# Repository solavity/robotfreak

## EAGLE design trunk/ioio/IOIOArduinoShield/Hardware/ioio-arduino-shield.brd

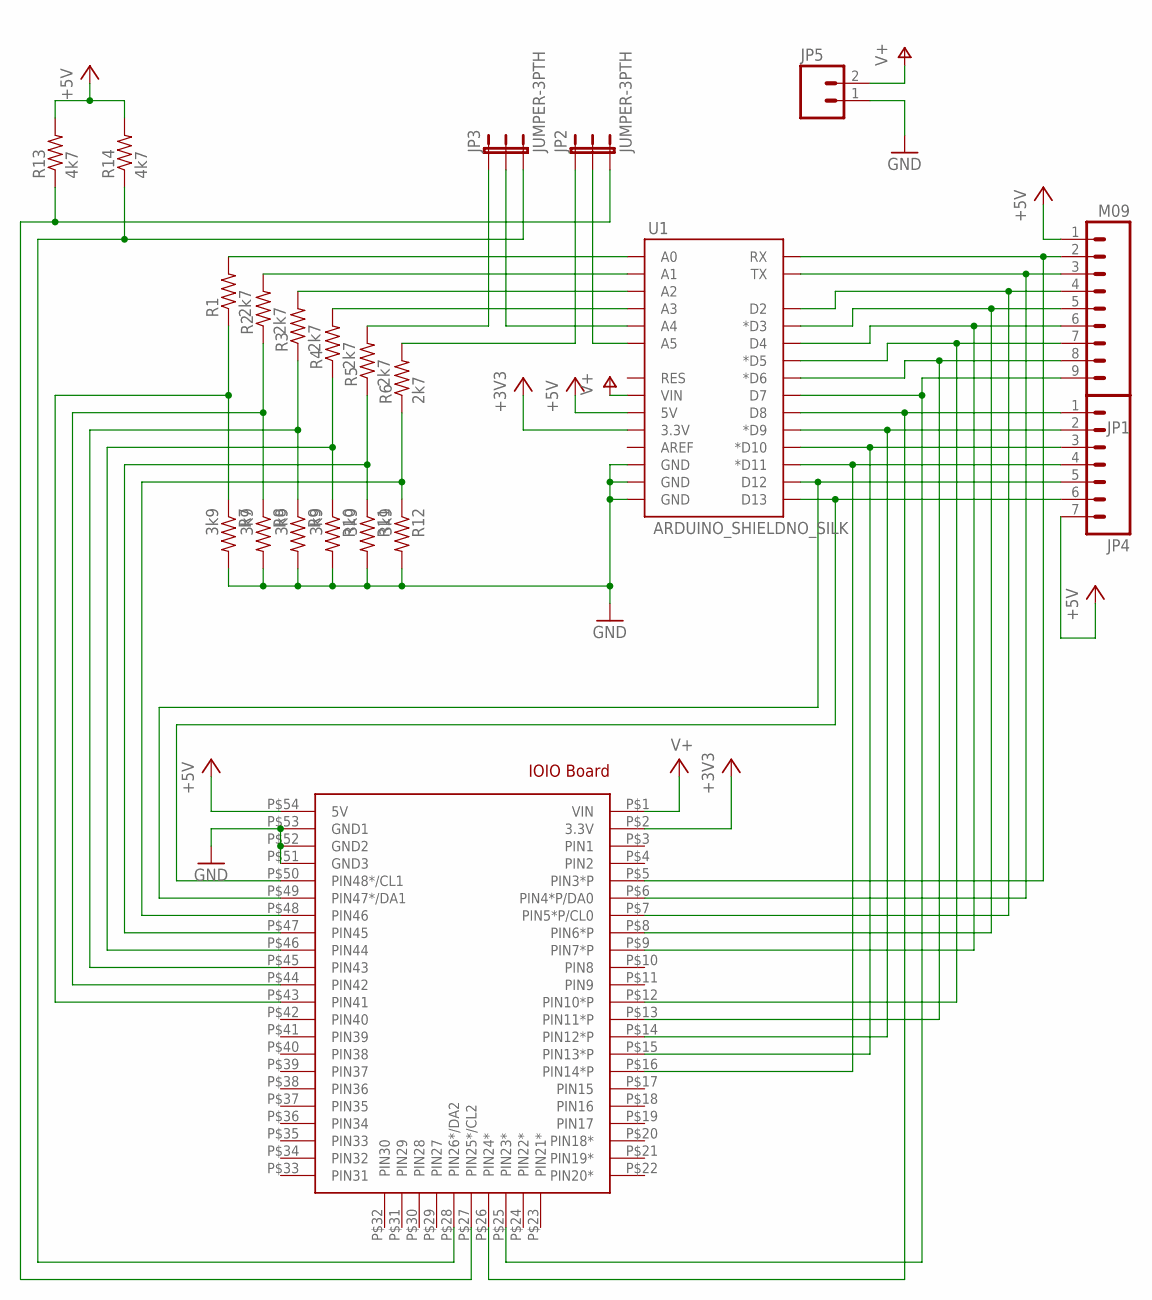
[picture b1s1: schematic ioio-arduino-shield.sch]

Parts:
JP1: M09; 1X09
JP2, JP3: JUMPER-3PTH; 1X03
JP4: M07; 1X07
JP5: M025MM; SCREWTERMINAL-5MM-2
R1, R2, R3, R4, R5, R6: 2k7; 0805
R7, R8, R9, R10, R11, R12: 3k9; 0805
R13, R14: 4k7; 0805
U1: ARDUINO_SHIELDNO_SILK; DUEMILANOVE_VIAS
U$1: IOIO

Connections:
+3V3: U1.3.3V, U$1.P$2 (3.3V)
+5V: JP1.1, JP4.7, R13.2, R14.2, U1.5V, U$1.P$54 (5V)
GND: JP5.1, R7.2, R8.2, R9.2, R10.2, R11.2, R12.2, U1.GND@0 (GND), U1.GND@1 (GND), U1.GND@2 (GND), U$1.P$51 (GND3), U$1.P$52 (GND2), U$1.P$53 (GND1)
unnamed: R1.2, U1.A0
unnamed: R2.2, U1.A1
unnamed: R3.2, U1.A2
unnamed: R4.2, U1.A3
unnamed: JP3.1, R5.2
unnamed: JP3.2, U1.A4
unnamed: JP2.1, R6.2
unnamed: JP2.2, U1.A5
unnamed: R1.1, R7.1, U$1.P$43 (PIN41)
unnamed: JP1.2, U1.RX, U$1.P$5 (PIN3*P)
unnamed: JP1.3, U1.TX, U$1.P$6 (PIN4*P/DA0)
unnamed: JP1.4, U1.D2, U$1.P$7 (PIN5*P/CL0)
unnamed: JP1.5, U1.D3 (*D3), U$1.P$8 (PIN6*P)
unnamed: U1.D4, U$1.P$9 (PIN7*P)
unnamed: JP1.7, U1.D5 (*D5), U$1.P$12 (PIN10*P)
unnamed: JP1.8, U1.D6 (*D6), U$1.P$13 (PIN11*P)
unnamed: JP4.1, U1.D8, U$1.P$26 (PIN24*)
unnamed: JP4.2, U1.D9 (*D9), U$1.P$14 (PIN12*P)
unnamed: JP4.3, U1.D10 (*D10), U$1.P$15 (PIN13*P)
unnamed: JP4.4, U1.D11 (*D11), U$1.P$16 (PIN14*P)
unnamed: JP4.5, U1.D12, U$1.P$49 (PIN47*/DA1)
unnamed: JP4.6, U1.D13, U$1.P$50 (PIN48*/CL1)
unnamed: R2.1, R8.1, U$1.P$44 (PIN42)
unnamed: R3.1, R9.1, U$1.P$45 (PIN43)
unnamed: R4.1, R10.1, U$1.P$46 (PIN44)
unnamed: R5.1, R11.1, U$1.P$47 (PIN45)
unnamed: R6.1, R12.1, U$1.P$48 (PIN46)
unnamed: U1.D7, U$1.P$25 (PIN23*)
unnamed: JP2.3, R13.1, U$1.P$27 (PIN25*/CL2)
unnamed: JP3.3, R14.1, U$1.P$28 (PIN26*/DA2)
V+: JP5.2, U1.VIN, U$1.P$1 (VIN)

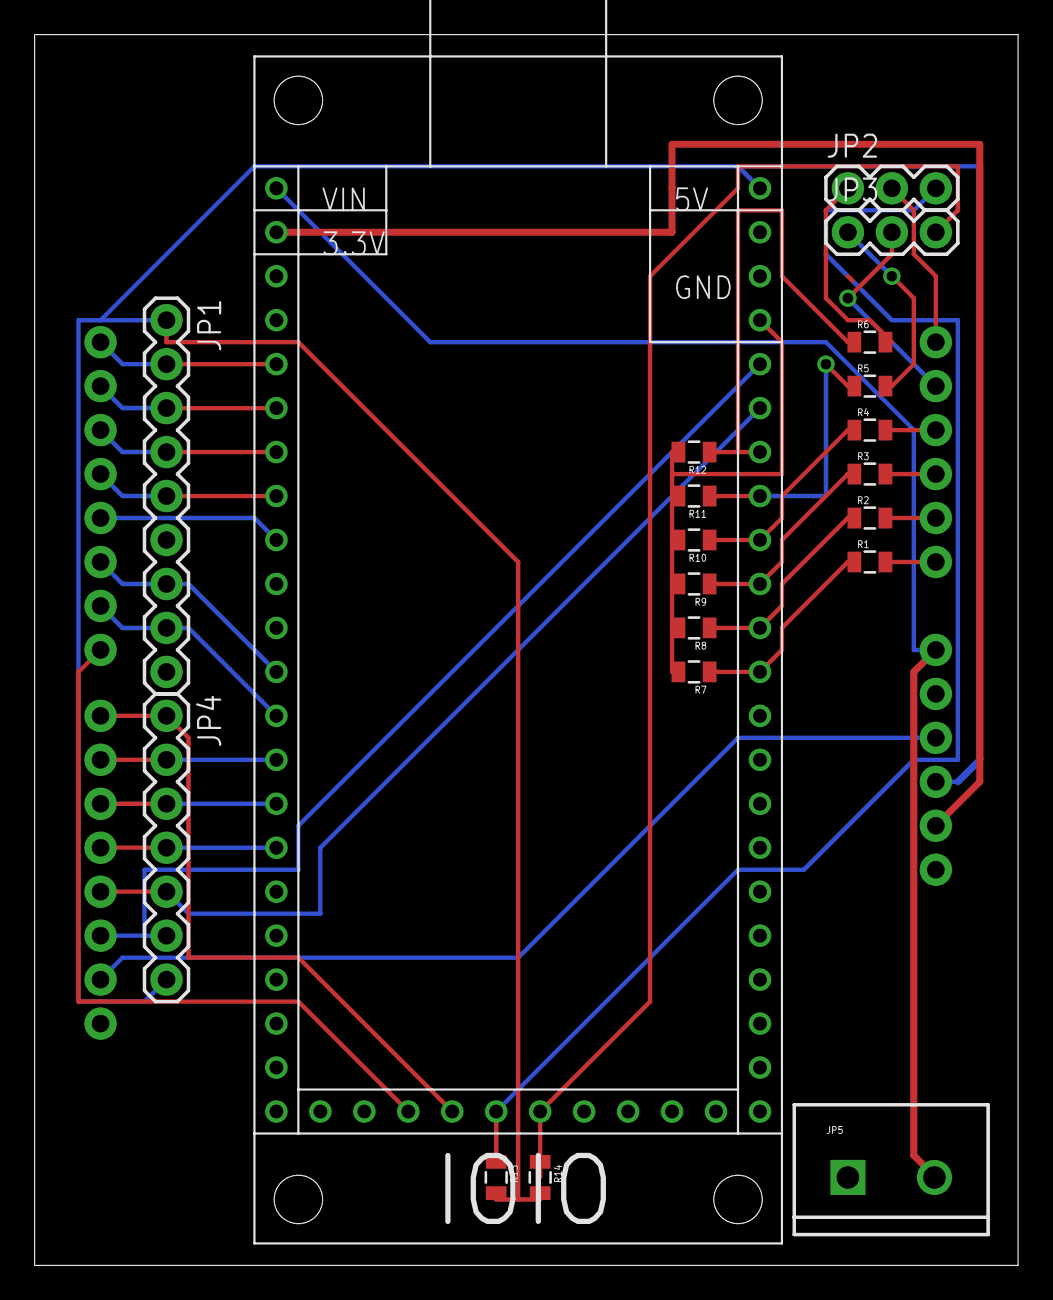
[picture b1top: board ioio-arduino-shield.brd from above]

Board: 2 copper layers, 56.8 x 71.1 mm, 21 parts (0 on the bottom side), 34 nets.

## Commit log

2009-10-29 Initial directory structure.
2009-10-29 initial release
2009-10-29 Created wiki page through web user interface.
2009-10-29 Edited wiki page through web user interface.
2010-09-04 Edited wiki page Pacman through web user interface.
2010-09-04 Pacman robot initial release
2010-09-15 new examples for Ardubot
2010-09-15 added Servos for mouth moving
2010-12-29 MASHR - initial release
2011-01-03 WII IR Camera Arduino/Processing sketches
2011-05-24 first connection to ADB
2011-05-25 Edited wiki page FezBridge through web user interface.
2011-05-25 Edited wiki page Robots through web user interface.
2011-05-25 port forwarding, parse incoming commands
2011-05-26 receiving and parsing of input data
2011-05-27 FezBridge almost working. Release 0.1
2011-12-24 IOIO-SHR initial release
2011-12-24 Edited wiki page IoioShr through web user interface.
2011-12-24 Edited wiki page Mashr through web user interface.
2012-01-04 IOIO Object follower
2012-03-14 IOIO Ultrasonic Sensor initlal release
2012-03-18 ADB Write function fixed
2012-04-01 IOIO-Arduino Shield Adapter initial release
2012-06-20 IOIO Rover5 initial release
2012-07-01 IOIO Rover5 User Interface for Android v4. initial release
2012-07-16 IOIO Rover. Different Modes of operation. New Motor controller
2012-07-16 IOIORoverUI BlinkM functionality added
2012-07-16 IOIORover5 updated to Android v4.x. New motor controller
2012-08-25 Sir Lancelot robot initial release
2012-08-27 IOIO-Rover Campus Party Version
2013-07-23 Actual projects: MURCS, MURtle, FrankenBoB, MakeyMakey, Drifter
2013-07-24 MURCS examples: Cellbot, ObstacleAvoider, LineSensorTest
2013-07-28 MURtle- Analog Wheel encoders via interrupt, some drawing examples added
2013-07-28 3rd party Arduino libraries added
2013-07-28 CellBot light
2013-07-28 AllInOne example: line follow, line follow + PID, wall follow, obstacle avoiding, remote control and mode change via Bluetooth
2013-07-28 Android Remote Controller added (App inventor)
2013-07-28 AllInOne example als Zip Archiv
2013-08-01 Frankenbob fixed turn mode. Poser.exe + settings
2013-08-01 Scratch projects added
2013-08-01 MURCS, MURtle last fixes
2013-08-31 BoBette CP 2013
2016-03-10 Migrating wiki contents from Google Code

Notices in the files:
parts and their libraries:
SparkFun-Boards: Licensing: CC v3.0 Share-Alike You are welcome to use this library for commercial purposes.
